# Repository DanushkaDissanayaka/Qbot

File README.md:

# Qbot
Arduino based multi funtional micro bot( 115mm)

## Built With

* [Arduino Mega](https://www.arduino.cc/) - single-board microcontrollers and microcontroller kit
## Demo video

## Robot Snapshot

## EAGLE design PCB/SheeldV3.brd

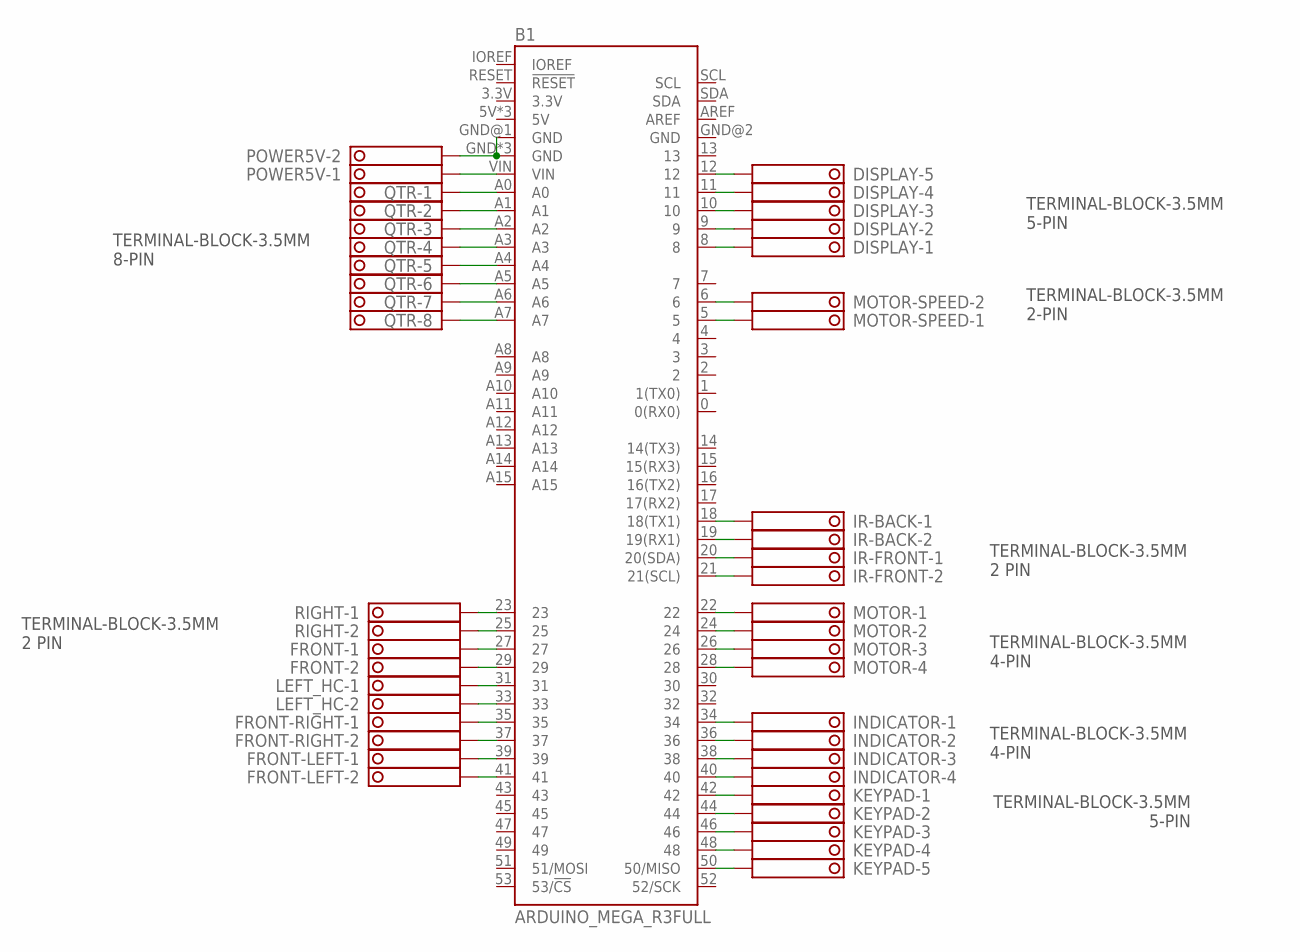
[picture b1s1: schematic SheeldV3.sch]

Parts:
B1: ARDUINO_MEGA_R3FULL; ARDUINO_MEGA_NO_SILK
DISPLAY: TERMINAL-BLOCK-3.5MM-5-PIN-LONG-PAD; TERMINAL-BLOCK-5-PIN-3.5MM-LONG-PAD
FRONT: TERMINAL-BLOCK-3.5MM-2-PIN-LONG-PAD; TERMINAL-BLOCK-2-PIN-3.5MM-LONG-PAD
FRONT-LEFT: TERMINAL-BLOCK-3.5MM-2-PIN-LONG-PAD; TERMINAL-BLOCK-2-PIN-3.5MM-LONG-PAD
FRONT-RIGHT: TERMINAL-BLOCK-3.5MM-2-PIN-LONG-PAD; TERMINAL-BLOCK-2-PIN-3.5MM-LONG-PAD
INDICATOR: TERMINAL-BLOCK-3.5MM-4-PIN-LONG-PAD; TERMINAL-BLOCK-4-PIN-3.5MM-LONG-PAD
IR-BACK: TERMINAL-BLOCK-3.5MM-2-PIN-LONG-PAD; TERMINAL-BLOCK-2-PIN-3.5MM-LONG-PAD
IR-FRONT: TERMINAL-BLOCK-3.5MM-2-PIN-LONG-PAD; TERMINAL-BLOCK-2-PIN-3.5MM-LONG-PAD
KEYPAD: TERMINAL-BLOCK-3.5MM-5-PIN-LONG-PAD; TERMINAL-BLOCK-5-PIN-3.5MM-LONG-PAD
LEFT_HC: TERMINAL-BLOCK-3.5MM-2-PIN-LONG-PAD; TERMINAL-BLOCK-2-PIN-3.5MM-LONG-PAD
MOTOR: TERMINAL-BLOCK-3.5MM-4-PIN-LONG-PAD; TERMINAL-BLOCK-4-PIN-3.5MM-LONG-PAD
MOTOR-SPEED: TERMINAL-BLOCK-3.5MM-2-PIN-LONG-PAD; TERMINAL-BLOCK-2-PIN-3.5MM-LONG-PAD
POWER5V: TERMINAL-BLOCK-3.5MM-2-PIN-LONG-PAD; TERMINAL-BLOCK-2-PIN-3.5MM-LONG-PAD
QTR: TERMINAL-BLOCK-3.5MM-8-PIN-LONG-PAD; TERMINAL-BLOCK-8-PIN-3.5MM-LONG-PAD
RIGHT: TERMINAL-BLOCK-3.5MM-2-PIN-LONG-PAD; TERMINAL-BLOCK-2-PIN-3.5MM-LONG-PAD

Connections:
unnamed: B1.12, DISPLAY.5
unnamed: B1.11, DISPLAY.4
unnamed: B1.10, DISPLAY.3
unnamed: B1.9, DISPLAY.2
unnamed: B1.8, DISPLAY.1
unnamed: B1.VIN, POWER5V.1
unnamed: B1.23, RIGHT.1
unnamed: B1.25, RIGHT.2
unnamed: B1.27, FRONT.1
unnamed: B1.29, FRONT.2
unnamed: B1.31, LEFT_HC.1
unnamed: B1.33, LEFT_HC.2
unnamed: B1.35, FRONT-RIGHT.1
unnamed: B1.37, FRONT-RIGHT.2
unnamed: B1.39, FRONT-LEFT.1
unnamed: B1.41, FRONT-LEFT.2
unnamed: B1.42, KEYPAD.1
unnamed: B1.44, KEYPAD.2
unnamed: B1.46, KEYPAD.3
unnamed: B1.48, KEYPAD.4
unnamed: B1.50 (50/MISO), KEYPAD.5
unnamed: B1.22, MOTOR.1
unnamed: B1.24, MOTOR.2
unnamed: B1.26, MOTOR.3
unnamed: B1.28, MOTOR.4
unnamed: B1.34, INDICATOR.1
unnamed: B1.36, INDICATOR.2
unnamed: B1.38, INDICATOR.3
unnamed: B1.40, INDICATOR.4
unnamed: B1.6, MOTOR-SPEED.2
unnamed: B1.5, MOTOR-SPEED.1
unnamed: B1.21 (21(SCL)), IR-FRONT.2
unnamed: B1.20 (20(SDA)), IR-FRONT.1
unnamed: B1.19 (19(RX1)), IR-BACK.2
unnamed: B1.18 (18(TX1)), IR-BACK.1
unnamed: B1.GND, B1.GND@1 (GND), B1.GND@3 (GND), B1.GND@4 (GND), POWER5V.2
unnamed: B1.A0, QTR.1
unnamed: B1.A1, QTR.2
unnamed: B1.A2, QTR.3
unnamed: B1.A3, QTR.4
unnamed: B1.A4, QTR.5
unnamed: B1.A5, QTR.6
unnamed: B1.A6, QTR.7
unnamed: B1.A7, QTR.8

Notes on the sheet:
TERMINAL-BLOCK-3.5MM 2 PIN
TERMINAL-BLOCK-3.5MM 4-PIN
TERMINAL-BLOCK-3.5MM 5-PIN
TERMINAL-BLOCK-3.5MM 2-PIN
TERMINAL-BLOCK-3.5MM 8-PIN

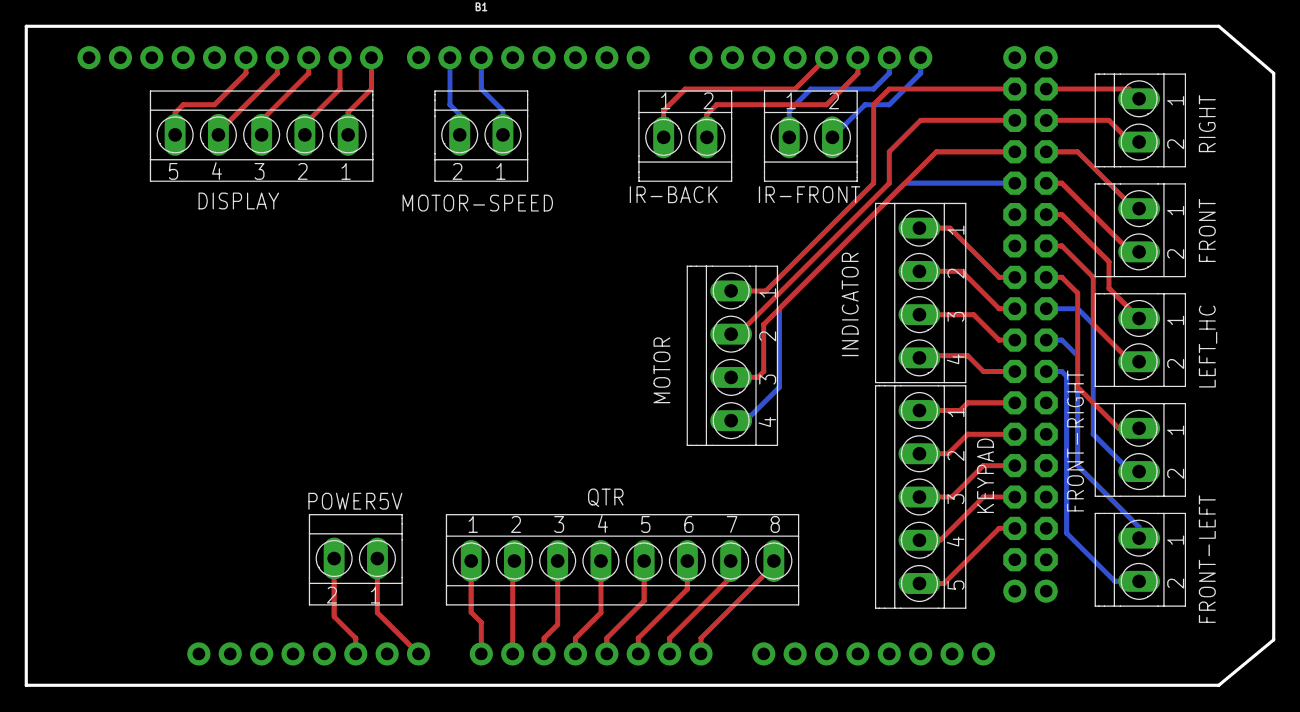
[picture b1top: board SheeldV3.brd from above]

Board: 2 copper layers, 101.0 x 53.3 mm, 15 parts (0 on the bottom side), 44 nets.

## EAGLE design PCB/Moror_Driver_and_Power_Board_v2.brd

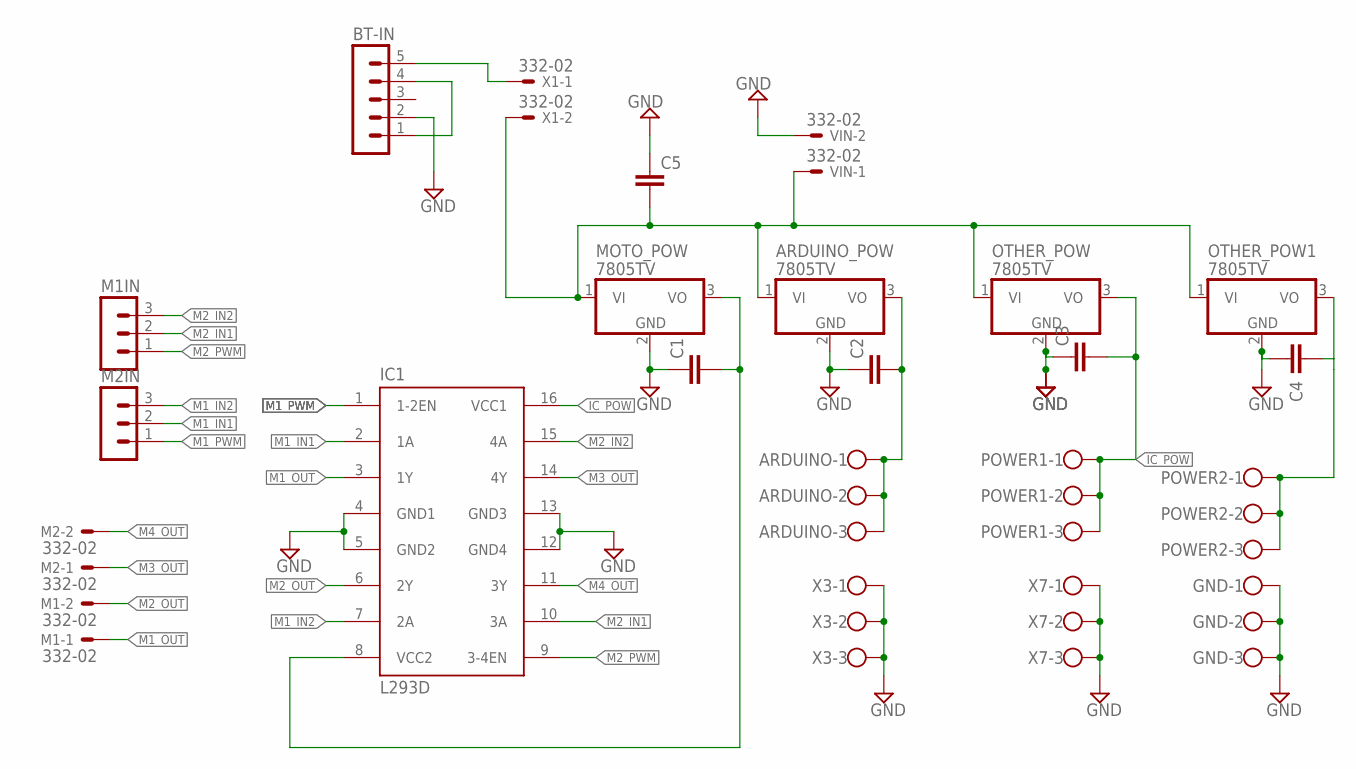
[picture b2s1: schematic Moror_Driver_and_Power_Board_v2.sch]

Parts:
ARDUINO: W237-103
ARDUINO_POW: 7805TV; TO220V
BT-IN: MA05-1
C1, C2, C3, C4, C5: C-EU025-030X050; C025-030X050
GND: W237-103
IC1: L293D; DIL16
M1, M2: 332-02
M1IN, M2IN: MA03-1
MOTO_POW: 7805TV; TO220V
OTHER_POW, OTHER_POW1: 7805TV; TO220V
POWER1, POWER2: W237-103
VIN: 332-02
X1: 332-02
X3, X7: W237-103

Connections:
GND: ARDUINO_POW.2 (GND), BT-IN.2, C1.1, C2.1, C3.1, C4.1, C5.1, GND.1, GND.2, GND.3, IC1.4 (GND1), IC1.5 (GND2), IC1.12 (GND4), IC1.13 (GND3), MOTO_POW.2 (GND), OTHER_POW.2 (GND), OTHER_POW1.2 (GND), VIN.2, X3.1, X3.2, X3.3, X7.1, X7.2, X7.3
IC_POW: C3.2, IC1.16 (VCC1), OTHER_POW.3 (VO), POWER1.1, POWER1.2, POWER1.3
M1_IN1: IC1.2 (1A), M2IN.2
M1_IN2: IC1.7 (2A), M2IN.3
M1_OUT: IC1.3 (1Y), M1.1
M1_PWM: IC1.1 (1-2EN), M2IN.1
M2_IN1: IC1.10 (3A), M1IN.2
M2_IN2: IC1.15 (4A), M1IN.3
M2_OUT: IC1.6 (2Y), M1.2
M2_PWM: IC1.9 (3-4EN), M1IN.1
M3_OUT: IC1.14 (4Y), M2.1
M4_OUT: IC1.11 (3Y), M2.2
unnamed: ARDUINO_POW.1 (VI), C5.2, MOTO_POW.1 (VI), OTHER_POW.1 (VI), OTHER_POW1.1 (VI), VIN.1, X1.2
unnamed: BT-IN.1, BT-IN.4
unnamed: BT-IN.5, X1.1
unnamed: C1.2, IC1.8 (VCC2), MOTO_POW.3 (VO)
unnamed: C4.2, OTHER_POW1.3 (VO), POWER2.1, POWER2.2, POWER2.3
VCC: ARDUINO.1, ARDUINO.2, ARDUINO.3, ARDUINO_POW.3 (VO), C2.2

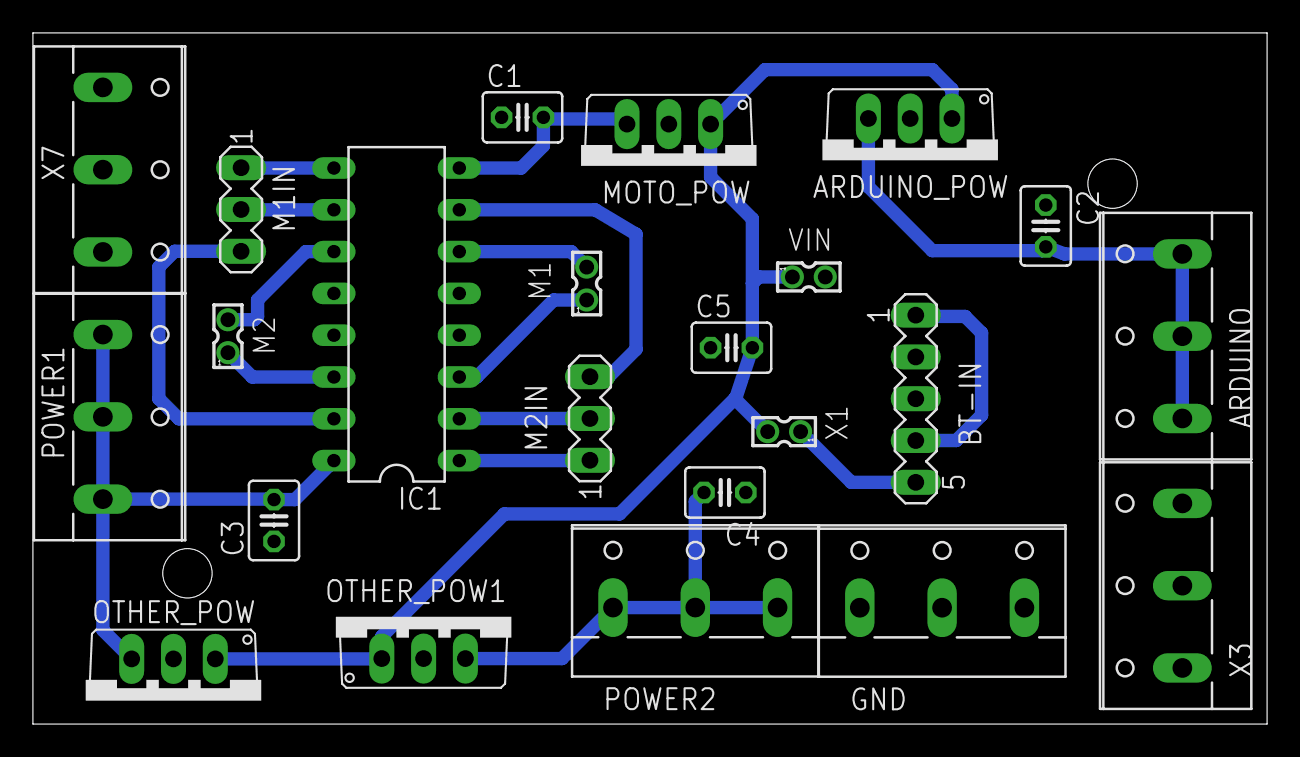
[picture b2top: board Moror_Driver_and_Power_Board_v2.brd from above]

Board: 2 copper layers, 75.0 x 42.0 mm, 23 parts (0 on the bottom side), 18 nets.

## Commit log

2018-11-30 Init Commit
2018-11-30 test comment
2018-11-30 test 2
2018-11-30 done line follow
2018-12-04 Tune line fllow brffore change position
2018-12-10 Bigin wallfllow
2018-12-10 Done turn tunung
2018-12-11 Line maze done
2018-12-11 Done wall ditection
2018-12-11 finish wall recognize
2018-12-12 done
2019-02-15 Code corrected and finalized wallfallow
2019-06-16 image added
2020-10-29 PCB design added
2020-10-29 Image added.
2020-10-29 Read me change

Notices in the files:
parts and their libraries:
SparkFun-Boards: Licensing: Creative Commons ShareAlike 4.0 International - https://creativecommons.org/licenses/by-sa/4.0
